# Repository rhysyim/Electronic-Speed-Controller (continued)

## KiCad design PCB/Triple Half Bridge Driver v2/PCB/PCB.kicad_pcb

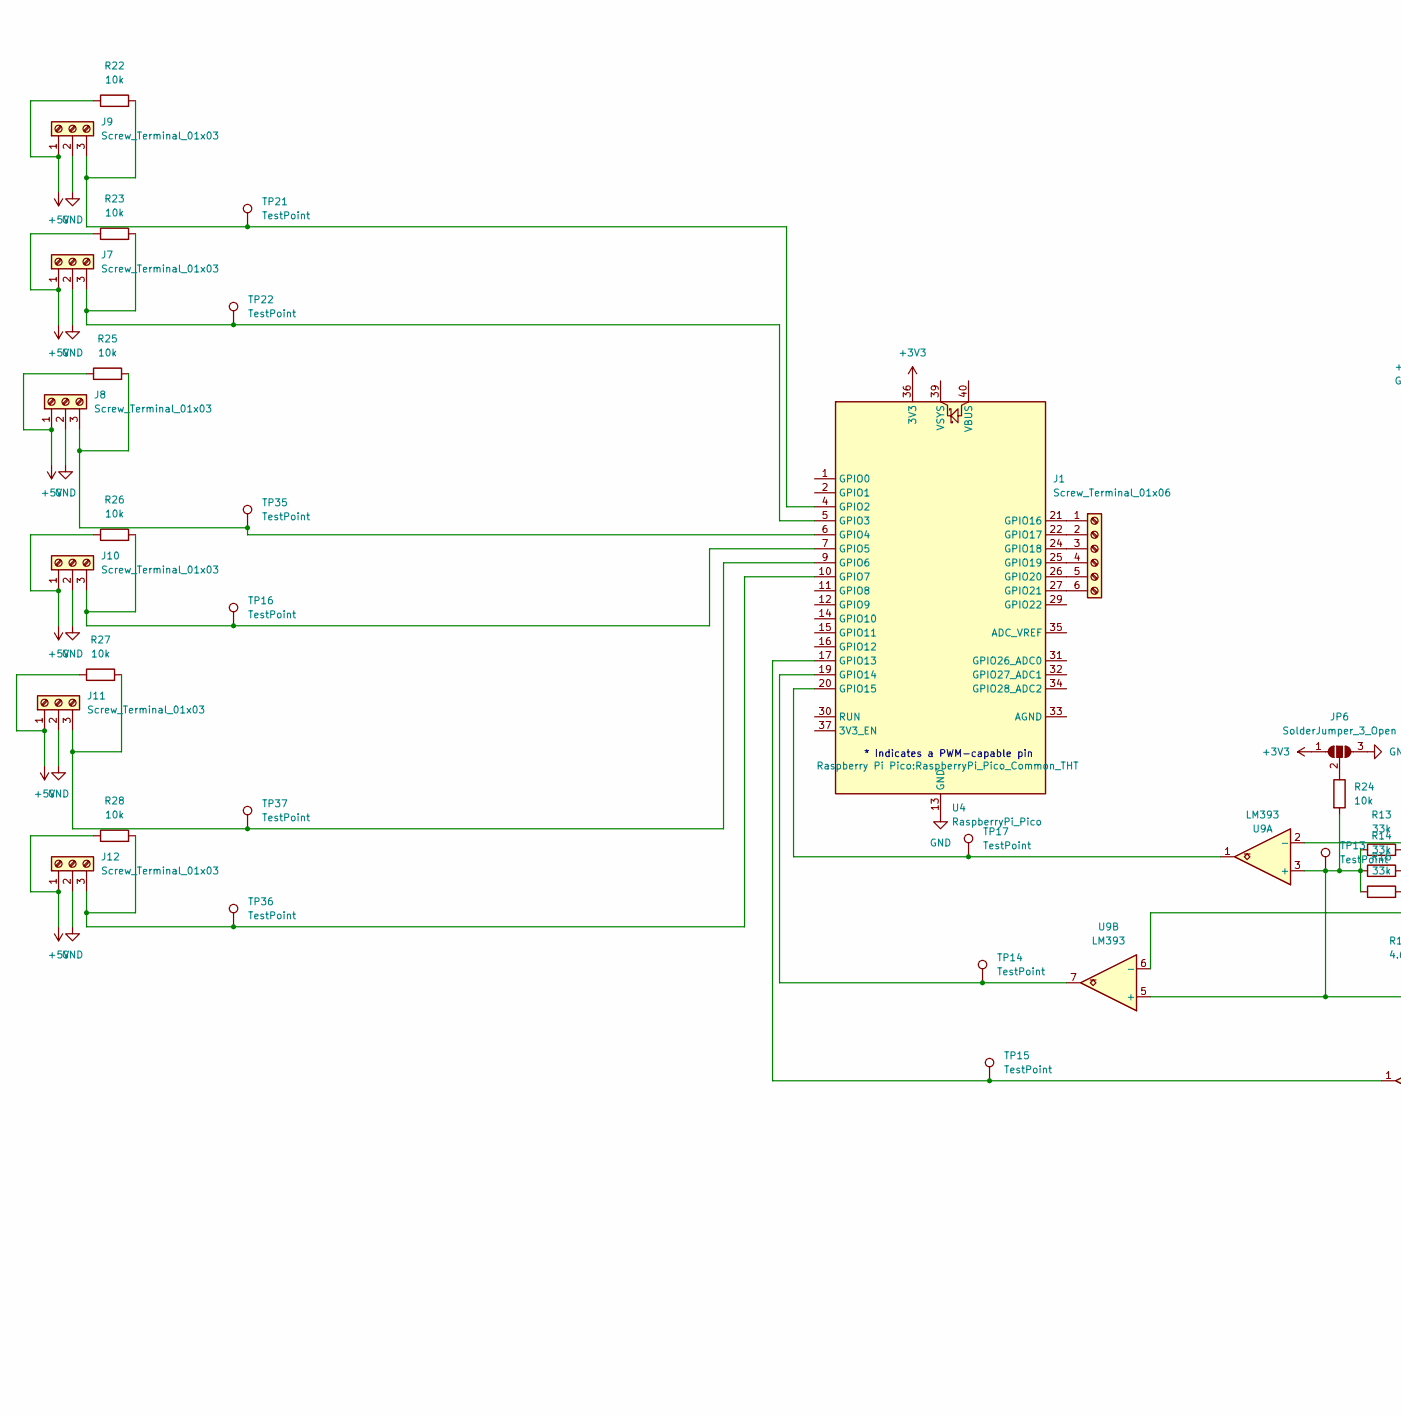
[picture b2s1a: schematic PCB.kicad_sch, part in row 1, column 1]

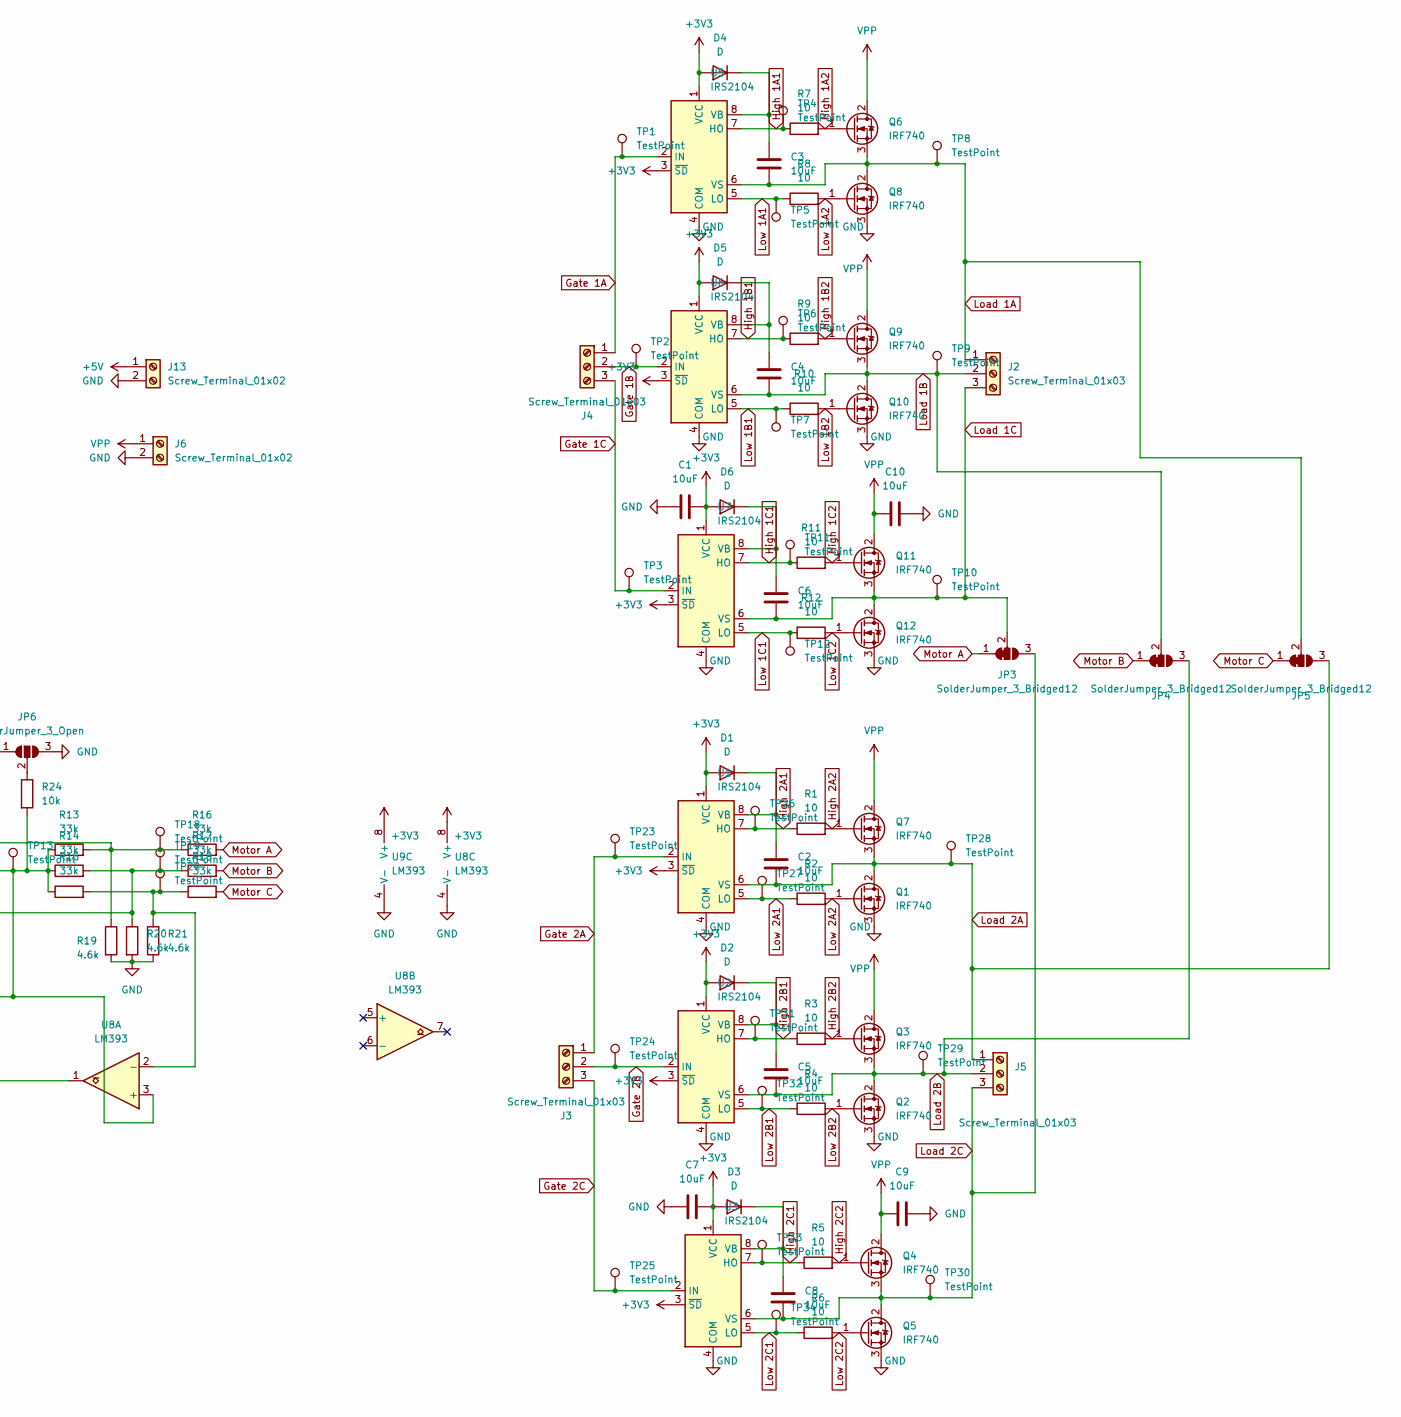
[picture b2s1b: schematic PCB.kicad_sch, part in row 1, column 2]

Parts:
C1, C2, C3, C4, C5, C6, C7, C8, C9, C10: 10uF; C_Rect_L7.0mm_W4.5mm_P5.00mm
D1, D2, D3, D4, D5, D6: D; D_A-405_P7.62mm_Horizontal
J1: Screw_Terminal_01x06; PinHeader_1x06_P2.54mm_Vertical
J2, J5: Screw_Terminal_01x03; 1792876
J3, J4, J7, J8, J9, J10, J11, J12: Screw_Terminal_01x03; PinHeader_1x03_P2.54mm_Vertical
J6: Screw_Terminal_01x02; 1792863
J13: Screw_Terminal_01x02; PinSocket_1x02_P2.54mm_Vertical
JP3, JP4, JP5: SolderJumper_3_Bridged12; SolderJumper-3_P2.0mm_Open_TrianglePad1.0x1.5mm
JP6: SolderJumper_3_Open; SolderJumper-3_P1.3mm_Open_Pad1.0x1.5mm
Q1, Q2, Q3, Q4, Q5, Q6, Q7, Q8, Q9, Q10, Q11, Q12: IRF740; TO-220-3_Vertical
R1, R2, R3, R4, R5, R6, R7, R8, R9, R10, R11, R12: 10; R_Axial_DIN0207_L6.3mm_D2.5mm_P7.62mm_Horizontal
R13, R14, R15, R16, R17, R18: 33k; R_Axial_DIN0207_L6.3mm_D2.5mm_P7.62mm_Horizontal
R19, R20, R21: 4.6k; R_Axial_DIN0207_L6.3mm_D2.5mm_P7.62mm_Horizontal
R22, R23, R24, R25, R26, R27, R28: 10k; R_Axial_DIN0207_L6.3mm_D2.5mm_P7.62mm_Horizontal
TP1, TP2, TP3, TP4, TP5, TP6, TP7, TP8, TP9, TP10, TP11, TP12, TP13, TP14, TP15, TP16, TP17, TP18, TP19, TP20, TP21, TP22, TP23, TP24, TP25, TP26, TP27, TP28, TP29, TP30, TP31, TP32, TP33, TP34, TP35, TP36, TP37: TestPoint; TestPoint_THTPad_2.0x2.0mm_Drill1.0mm
U1, U2, U3, U5, U6, U7: IRS2104; DIP-8_W7.62mm
U4: RaspberryPi_Pico; RaspberryPi_Pico_Common_THT
U8, U9: LM393; DIP-8_W7.62mm

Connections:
+3V3: C1.2, C7.2, D1.2 (A), D2.2 (A), D3.2 (A), D4.2 (A), D5.2 (A), D6.2 (A), JP6.1 (A), U1.1 (VCC), U1.3 (~SD), U2.1 (VCC), U2.3 (~SD), U3.1 (VCC), U3.3 (~SD), U4.36 (3V3), U5.1 (VCC), U5.3 (~SD), U6.1 (VCC), U6.3 (~SD), U7.1 (VCC), U7.3 (~SD), U8.8 (V+), U9.8 (V+)
+5V: J7.1, J8.1, J9.1, J10.1, J11.1, J12.1, J13.1, R22.1, R23.1, R25.1, R26.1, R27.1, R28.1
GND: C1.1, C7.1, C9.2, C10.2, J6.2, J7.2, J8.2, J9.2, J10.2, J11.2, J12.2, J13.2, JP6.3 (B), Q1.3 (S), Q2.3 (S), Q5.3 (S), Q8.3 (S), Q10.3 (S), Q12.3 (S), R19.2, R20.2, R21.1, U1.4 (COM), U2.4 (COM), U3.4 (COM), U4.3 (GND), U4.8 (GND), U4.13 (GND), U4.18 (GND), U4.23 (GND), U4.28 (GND), U4.38 (GND), U5.4 (COM), U6.4 (COM), U7.4 (COM), U8.4 (V-), U9.4 (V-)
Gate 1A: J4.1, TP1.1, U5.2 (IN)
Gate 1B: J4.2, TP2.1, U6.2 (IN)
Gate 1C: J4.3, TP3.1, U7.2 (IN)
Gate 2A: J3.1, TP23.1, U1.2 (IN)
Gate 2B: J3.2, TP24.1, U2.2 (IN)
Gate 2C: J3.3, TP25.1, U3.2 (IN)
High 1A1: R7.1, TP4.1, U5.7 (HO)
High 1A2: Q6.1 (G), R7.2
High 1B1: R9.1, TP6.1, U6.7 (HO)
High 1B2: Q9.1 (G), R9.2
High 1C1: R11.1, TP11.1, U7.7 (HO)
High 1C2: Q11.1 (G), R11.2
High 2A1: R1.1, TP26.1, U1.7 (HO)
High 2A2: Q7.1 (G), R1.2
High 2B1: R3.1, TP31.1, U2.7 (HO)
High 2B2: Q3.1 (G), R3.2
High 2C1: R5.1, TP33.1, U3.7 (HO)
High 2C2: Q4.1 (G), R5.2
Load 1A: C3.2, J2.1, JP5.2 (C), Q6.3 (S), Q8.2 (D), TP8.1, U5.6 (VS)
Load 1B: C4.2, J2.2, JP4.2 (C), Q9.3 (S), Q10.2 (D), TP9.1, U6.6 (VS)
Load 1C: C6.2, J2.3, JP3.2 (C), Q11.3 (S), Q12.2 (D), TP10.1, U7.6 (VS)
Load 2A: C2.2, J5.1, JP5.3 (B), Q1.2 (D), Q7.3 (S), TP28.1, U1.6 (VS)
Load 2B: C5.2, J5.2, JP4.3 (B), Q2.2 (D), Q3.3 (S), TP29.1, U2.6 (VS)
Load 2C: C8.2, J5.3, JP3.3 (B), Q4.3 (S), Q5.2 (D), TP30.1, U3.6 (VS)
Low 1A1: R8.1, TP5.1, U5.5 (LO)
Low 1A2: Q8.1 (G), R8.2
Low 1B1: R10.1, TP7.1, U6.5 (LO)
Low 1B2: Q10.1 (G), R10.2
Low 1C1: R12.1, TP12.1, U7.5 (LO)
Low 1C2: Q12.1 (G), R12.2
Low 2A1: R2.1, TP27.1, U1.5 (LO)
Low 2A2: Q1.1 (G), R2.2
Low 2B1: R4.1, TP32.1, U2.5 (LO)
Low 2B2: Q2.1 (G), R4.2
Low 2C1: R6.1, TP34.1, U3.5 (LO)
Low 2C2: Q5.1 (G), R6.2
Motor A: JP3.1 (A), R16.2
Motor B: JP4.1 (A), R17.2
Motor C: JP5.1 (A), R18.2
unnamed: C2.1, D1.1 (K), U1.8 (VB)
unnamed: C5.1, D2.1 (K), U2.8 (VB)
unnamed: C8.1, D3.1 (K), U3.8 (VB)
unnamed: C3.1, D4.1 (K), U5.8 (VB)
unnamed: C4.1, D5.1 (K), U6.8 (VB)
unnamed: C6.1, D6.1 (K), U7.8 (VB)
unnamed: J1.1, U4.21 (GPIO16)
unnamed: J1.2, U4.22 (GPIO17)
unnamed: J1.3, U4.24 (GPIO18)
unnamed: J1.4, U4.25 (GPIO19)
unnamed: J1.5, U4.26 (GPIO20)
unnamed: J1.6, U4.27 (GPIO21)
unnamed: J7.3, R23.2, TP22.1, U4.5 (GPIO3)
unnamed: J8.3, R25.2, TP35.1, U4.6 (GPIO4)
unnamed: J9.3, R22.2, TP21.1, U4.4 (GPIO2)
unnamed: J10.3, R26.2, TP16.1, U4.7 (GPIO5)
unnamed: J11.3, R27.2, TP37.1, U4.9 (GPIO6)
unnamed: J12.3, R28.2, TP36.1, U4.10 (GPIO7)
unnamed: JP6.2 (C), R24.1
unnamed: TP15.1, U4.17 (GPIO13), U8.1
unnamed: TP14.1, U4.19 (GPIO14), U9.7
unnamed: TP17.1, U4.20 (GPIO15), U9.1
unnamed: R13.1, R14.1, R15.1, R24.2, TP13.1, U8.3 (+), U9.3 (+), U9.5 (+)
unnamed: R15.2, R18.1, R21.2, TP20.1, U8.2 (-)
unnamed: R13.2, R16.1, R19.1, TP18.1, U9.2 (-)
unnamed: R14.2, R17.1, R20.1, TP19.1, U9.6 (-)
VPP: C9.1, C10.1, J6.1, Q3.2 (D), Q4.2 (D), Q6.2 (D), Q7.2 (D), Q9.2 (D), Q11.2 (D)

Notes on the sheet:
* Indicates a PWM-capable pin

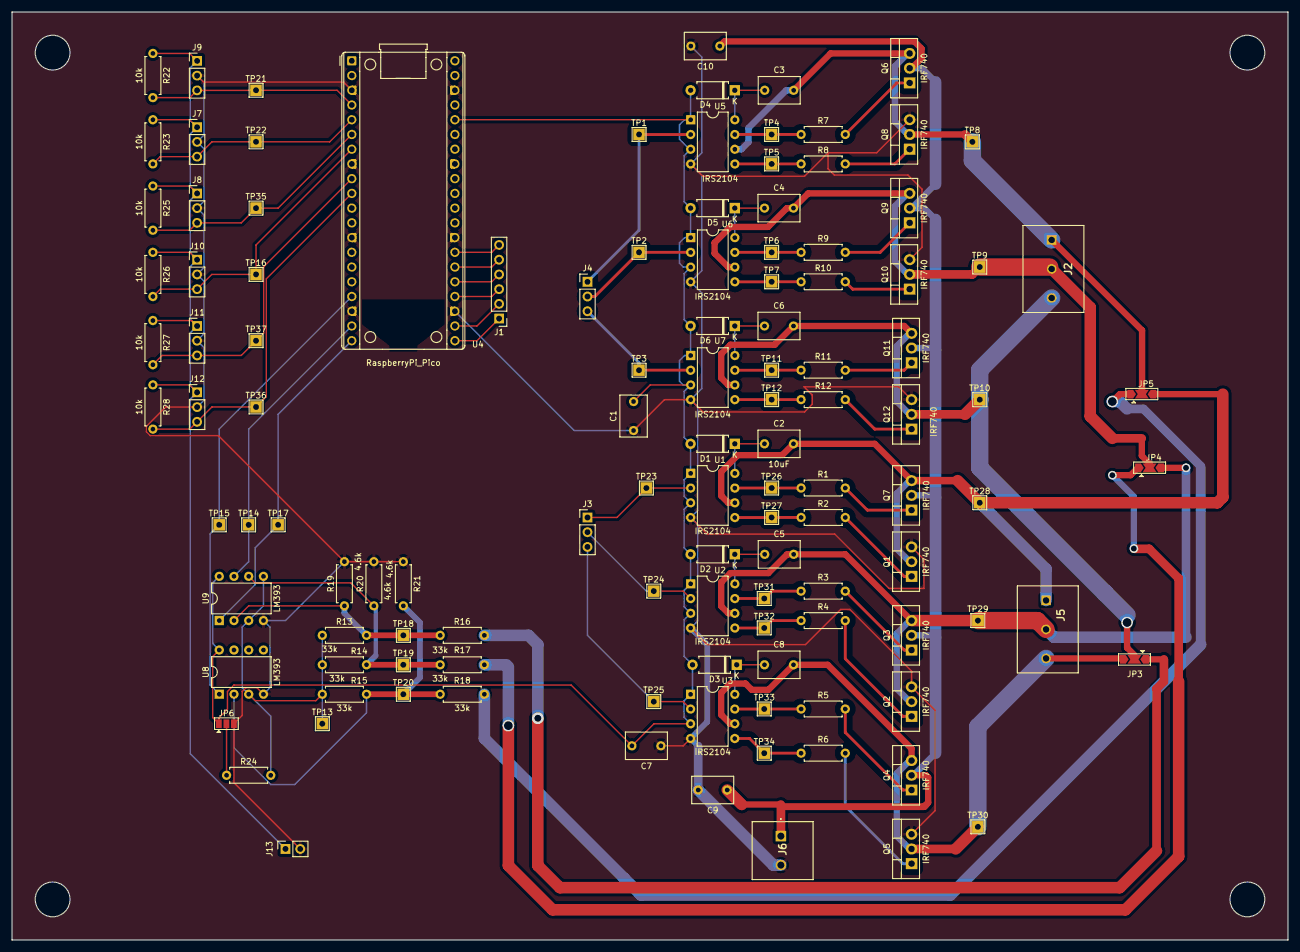
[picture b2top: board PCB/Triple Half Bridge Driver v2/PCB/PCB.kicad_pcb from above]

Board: 2 copper layers, 220.0 x 160.0 mm, 119 parts (0 on the bottom side), 69 nets.

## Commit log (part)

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2023-07-07 Change micros() data type
2023-12-26 Add ESC v5
2024-10-21 Update ESC code for PCB layout with Pi Pico
2024-11-02 Update PWM for phase 2
2024-11-29 Add PCB schematics v3
2024-11-30 Update code for ESC
2024-12-07 Add tracks for PCB
2024-12-08 Refactor
2024-12-10 Add trapezoidal code for ESC
2024-12-15 Update code to use PWM slice
2024-12-15 Update PCB
2024-12-16 Slightly optimize PCB tracks
2025-01-19 Fix potentiometer footprint and overlapping silkscreen on PCB
2025-02-16 Update Gerber files
2025-03-29 Add PCB, Schematics
2025-11-08 Adjust sinusoidal frequency
2025-11-10 Add ESC Issues Writeup
2025-11-23 Upload updated code
2025-11-23 Add notes on PWM frequency and control issues
    Document issues with PWM frequency and control modes.
2025-12-31 Add thermistor code
2025-12-31 Refactor temperature monitoring code for ADS1015
2025-12-31 Add markdown file for address connection
2025-12-31 Fix markdown header formatting in README.md
2025-12-31 Remove unnecessary blank lines in README.md
2026-02-05 Refactor thermistor instrumentation code
2026-02-05 Add code to scan for I2C on the port
2026-04-09 New version of PCB included, with more spacing between MOSFETs
2026-04-09 Revise README with hardware implementation details
    Updated the README to reflect hardware implementation details and changes in PCB versions.
2026-04-09 Remove unused gerber files
2026-04-15 Add datasheets for components used
2026-04-26 Update I2C SDA/SCL pins and improve ADC readings
